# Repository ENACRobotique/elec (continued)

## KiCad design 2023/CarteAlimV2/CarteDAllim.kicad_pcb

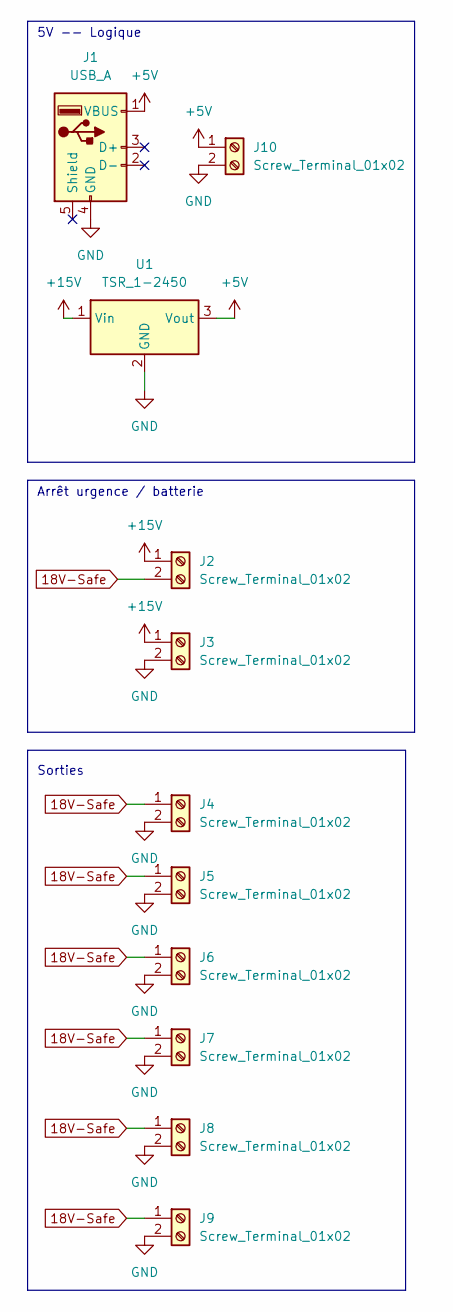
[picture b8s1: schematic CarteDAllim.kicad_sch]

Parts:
J1: USB_A; USB_A_Molex_67643_Horizontal
J2, J3, J4, J5, J6, J7, J8, J9, J10: Screw_Terminal_01x02; Altech_AK300_1x02_P5.00mm_45-Degree
U1: TSR_1-2450; Converter_DCDC_TRACO_TSR-1_THT

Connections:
18V-Safe: J2.2, J4.1, J5.1, J6.1, J7.1, J8.1, J9.1
+5V: J1.1 (VBUS), J10.1, U1.3 (Vout)
+15V: J2.1, J3.1, U1.1 (Vin)
GND: J1.4 (GND), J3.2, J4.2, J5.2, J6.2, J7.2, J8.2, J9.2, J10.2, U1.2 (GND)

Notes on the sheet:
Sorties
Arrêt urgence / batterie
5V -- Logique

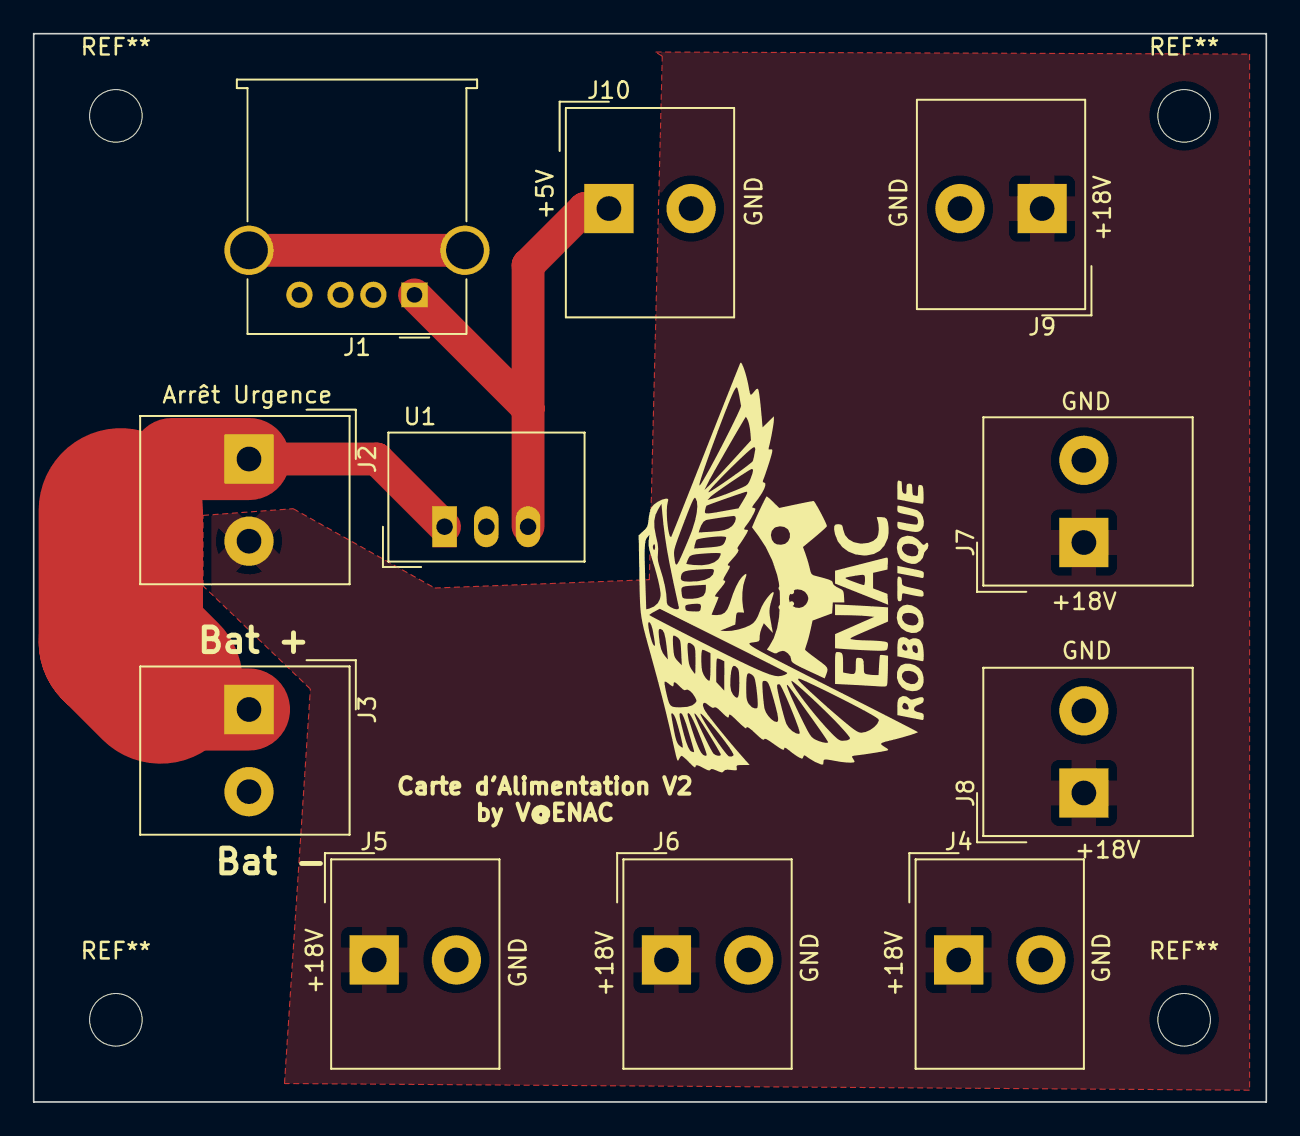
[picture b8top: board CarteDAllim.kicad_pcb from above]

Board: 2 copper layers, 75.0 x 65.0 mm, 11 parts (0 on the bottom side), 4 nets.
